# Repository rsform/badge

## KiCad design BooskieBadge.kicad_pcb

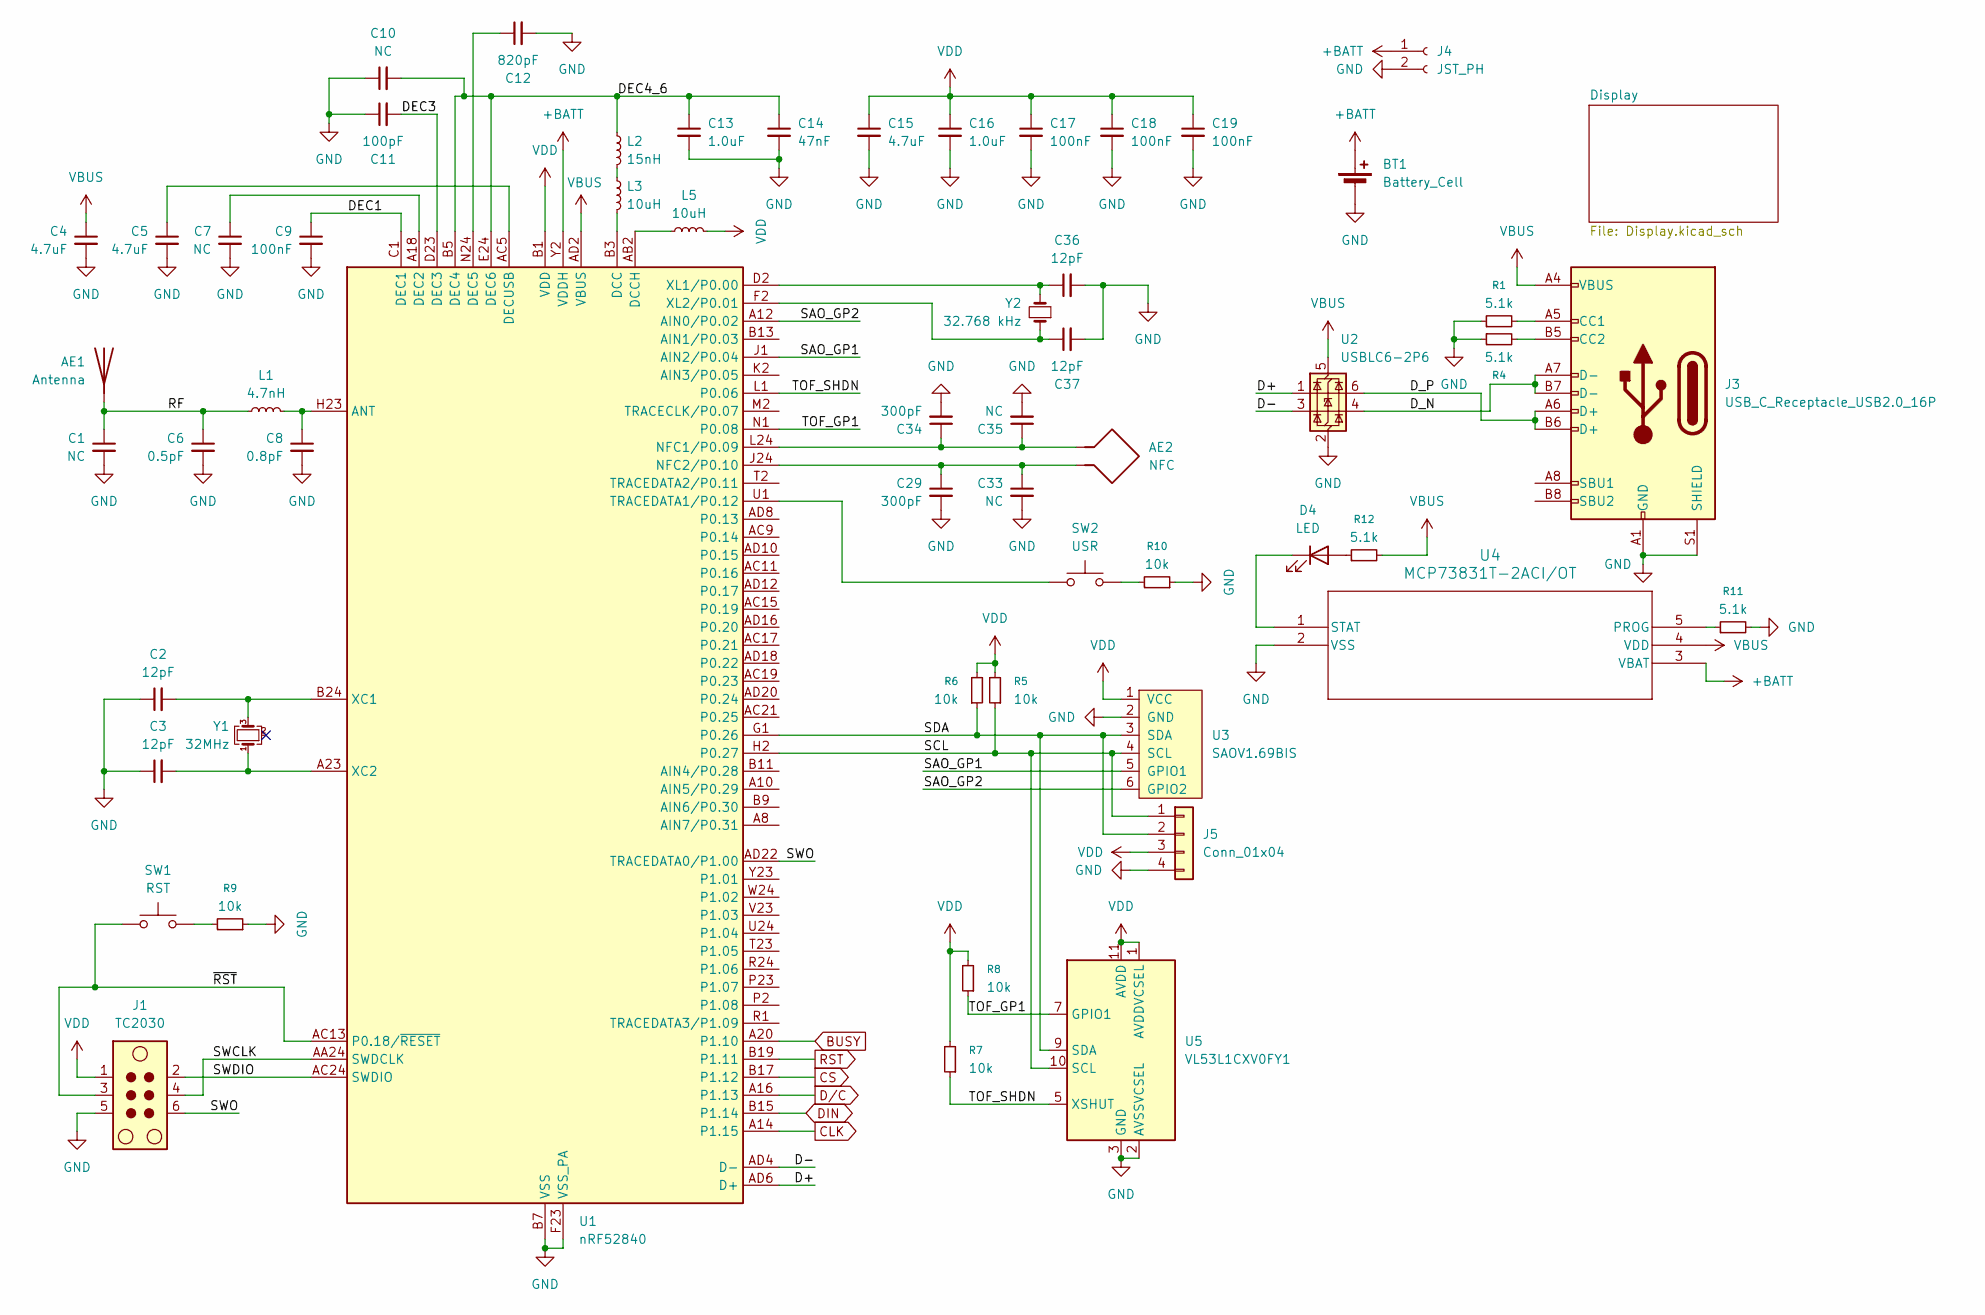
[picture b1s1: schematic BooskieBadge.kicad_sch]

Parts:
AE1: Antenna; 2.4GHz-meander-antenna-v2
AE2: NFC; NFC_ANTENNA
BT1: Battery_Cell; BAT_HOLDER_2032SMD
C1, C7, C10, C33, C35: NC; C_0402_1005Metric
C2, C3, C36, C37: 12pF; C_0402_1005Metric
C4, C5, C15: 4.7uF; C_0603_1608Metric
C6: 0.5pF; C_0402_1005Metric
C8: 0.8pF; C_0402_1005Metric
C9, C17, C18, C19: 100nF; C_0402_1005Metric
C11: 100pF; C_0402_1005Metric
C12: 820pF; C_0402_1005Metric
C13, C16: 1.0uF; C_0603_1608Metric
C14: 47nF; C_0402_1005Metric
C29, C34: 300pF; C_0402_1005Metric
D4: LED; LED_LB Q39G-L2OO-35-1_OSR
J1: TC2030; Tag-Connect_TC2030-IDC-NL_2x03_P1.27mm_Vertical
J3: USB_C_Receptacle_USB2.0_16P; USB_C_Receptacle_JAE_DX07S016JA1R1500
J4: JST_PH; JST_PH_S2B-PH-K_1x02_P2.00mm_Horizontal
J5: Conn_01x04; JST_SH_SM04B-SRSS-TB_1x04-1MP_P1.00mm_Horizontal
L1: 4.7nH; L_0402_1005Metric
L2: 15nH; L_0402_1005Metric
L3, L5: 10uH; L_0603_1608Metric
R1, R4, R11, R12: 5.1k; R_0402_1005Metric
R5, R6, R7, R8, R9, R10: 10k; R_0402_1005Metric
SW1: RST; SW_Push_1P1T_NO_CK_KMR2
SW2: USR; SW_Push_1P1T_NO_CK_KMR2
U1: nRF52840; Nordic_AQFN-73-1EP_7x7mm_P0.5mm
U2: USBLC6-2P6; SOT-666
U3: SAOV1.69BIS; Simple_Addon_v2-BADGE-2x3
U4: MCP73831T-2ACI/OT; SOT-23-5_MC_MCH
U5: VL53L1CXV0FY1; ST_VL53L1x
Y1: 32MHz; Crystal_SMD_2016-4Pin_2.0x1.6mm
Y2: 32.768 kHz; Crystal_SMD_3215-2Pin_3.2x1.5mm

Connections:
+BATT: BT1.1 (+), J4.1, U1.Y2 (VDDH), U4.3 (VBAT)
/D+: U1.AD6 (D+), U2.1 (I/O1)
/D-: U1.AD4 (D-), U2.3 (I/O2)
/DEC1: C9.1, U1.C1 (DEC1)
/DEC3: C11.2, U1.D23 (DEC3)
/DEC4_6: C10.2, C13.1, C14.1, L2.1, U1.B5 (DEC4), U1.E24 (DEC6)
/D_N: J3.A7 (D-), J3.B7 (D-), U2.4 (I/O2)
/D_P: J3.A6 (D+), J3.B6 (D+), U2.6 (I/O1)
/RF: AE1.1 (A), C1.1, C6.1, L1.1
/SAO_GP1: U1.J1 (AIN2/P0.04), U3.5 (GPIO1)
/SAO_GP2: U1.A12 (AIN0/P0.02), U3.6 (GPIO2)
/SCL: J5.1, R5.1, U1.H2 (P0.27), U3.4 (SCL), U5.10 (SCL)
/SDA: J5.2, R6.1, U1.G1 (P0.26), U3.3 (SDA), U5.9 (SDA)
/SWCLK: J1.4, U1.AA24 (SWDCLK)
/SWDIO: J1.2, U1.AC24 (SWDIO)
/SWO: J1.6, U1.AD22 (TRACEDATA0/P1.00)
/TOF_GP1: R8.1, U1.N1 (P0.08), U5.7 (GPIO1)
/TOF_SHDN: R7.1, U1.L1 (P0.06), U5.5 (XSHUT)
/~RST: J1.3, SW1.1, U1.AC13 (P0.18/~RESET)
BUSY: U1.A20 (P1.10); also elsewhere on the board
CLK: U1.A14 (P1.15); also elsewhere on the board
CS: U1.B17 (P1.12); also elsewhere on the board
DIN: U1.B15 (P1.14); also elsewhere on the board
D/C: U1.A16 (P1.13); also elsewhere on the board
GND: BT1.2 (-), C1.2, C2.1, C3.1, C4.2, C5.2, C6.2, C7.2, C8.2, C9.2, C10.1, C11.1, C12.2, C13.2, C14.2, C15.2, C16.2, C17.2, C18.2, C19.2, C29.2, C33.2, C34.2, C35.2, C36.2, C37.2, J1.5, J3.A1 (GND), J3.A12 (GND), J3.B1 (GND), J3.B12 (GND), J3.S1 (SHIELD), J4.2, J5.4, R1.1, R4.1, R9.1, R10.1, R11.2, U1.B7 (VSS), U1.EP (VSS), U1.F23 (VSS_PA), U2.2 (GND), U3.2 (GND), U4.2 (VSS), U5.2 (AVSSVCSEL), U5.3 (GND), U5.4 (GND), U5.6 (GND), U5.12 (GND); also elsewhere on the board
unnamed: D4.2 (A), R12.1
unnamed: D4.1 (K), U4.1 (STAT)
unnamed: J3.A5 (CC1), R1.2
unnamed: J3.B5 (CC2), R4.2
unnamed: L2.2, L3.1
unnamed: R9.2, SW1.2
unnamed: R10.2, SW2.2
unnamed: C8.1, L1.2, U1.H23 (ANT)
unnamed: L3.2, U1.B3 (DCC)
unnamed: L5.2, U1.AB2 (DCCH)
unnamed: C7.1, U1.A18 (DEC2)
unnamed: C12.1, U1.N24 (DEC5)
unnamed: C5.1, U1.AC5 (DECUSB)
unnamed: AE2.1, C34.1, C35.1, U1.L24 (NFC1/P0.09)
unnamed: AE2.2, C29.1, C33.1, U1.J24 (NFC2/P0.10)
unnamed: SW2.1, U1.U1 (TRACEDATA1/P0.12)
unnamed: C2.2, U1.B24 (XC1), Y1.3
unnamed: C3.2, U1.A23 (XC2), Y1.1
unnamed: C36.1, U1.D2 (XL1/P0.00), Y2.2
unnamed: C37.1, U1.F2 (XL2/P0.01), Y2.1
unnamed: R11.1, U4.5 (PROG)
RST: U1.B19 (P1.11); also elsewhere on the board
VBUS: C4.1, J3.A4 (VBUS), J3.A9 (VBUS), J3.B4 (VBUS), J3.B9 (VBUS), R12.2, U1.AD2 (VBUS), U2.5 (VBUS), U4.4 (VDD)
VDD: C15.1, C16.1, C17.1, C18.1, C19.1, J1.1, J5.3, L5.1, R5.2, R6.2, R7.2, R8.2, U1.A22 (VDD), U1.AD14 (VDD), U1.AD23 (VDD), U1.B1 (VDD), U1.W1 (VDD), U3.1 (VCC), U5.1 (AVDDVCSEL), U5.11 (AVDD); also elsewhere on the board

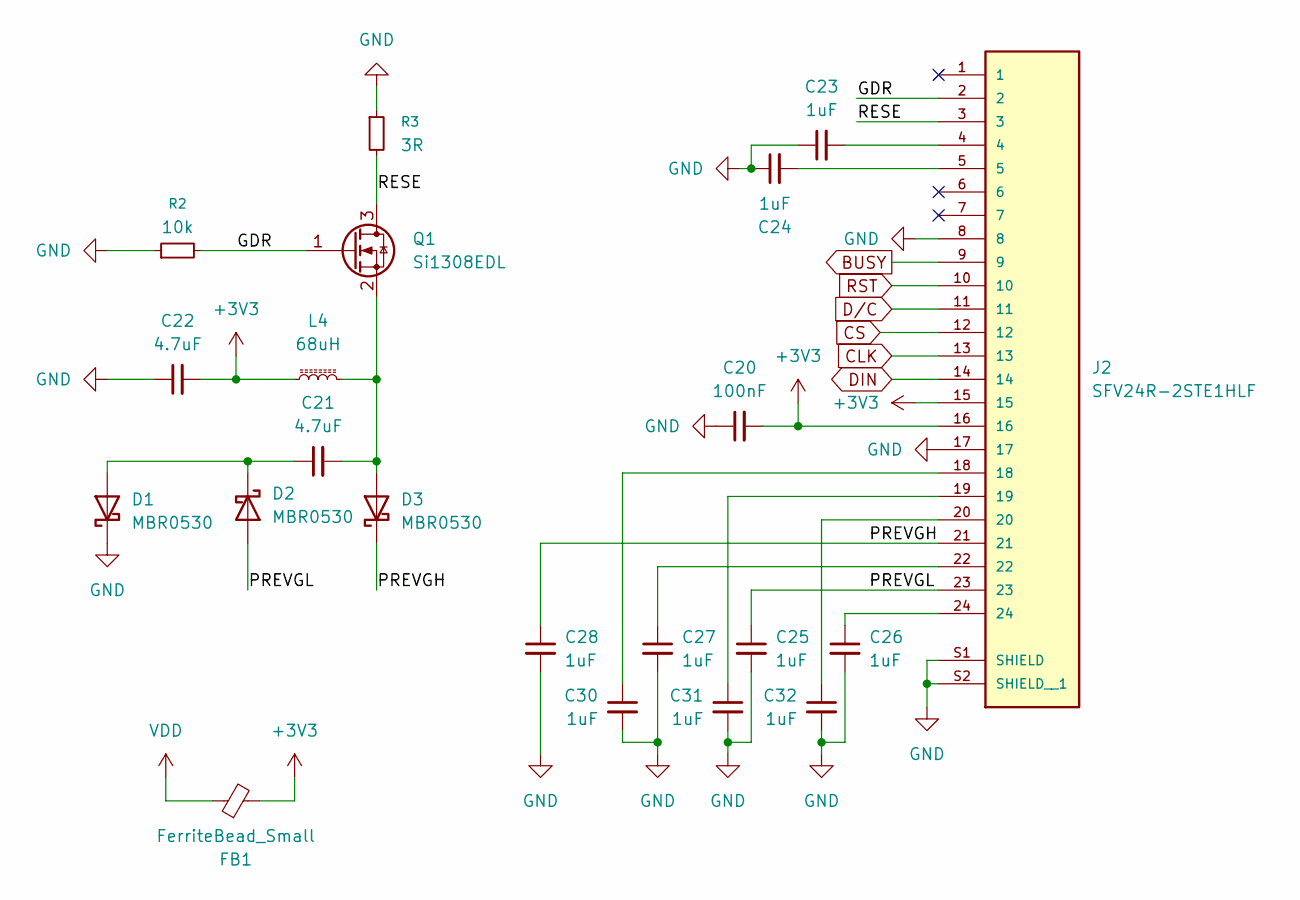
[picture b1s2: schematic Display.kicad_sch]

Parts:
C20: 100nF; C_0402_1005Metric
C21, C22: 4.7uF; C_0603_1608Metric
C23, C24, C25, C26, C27, C28, C30, C31, C32: 1uF; C_0603_1608Metric
D1, D2, D3: MBR0530; D_SOD-123
FB1: FerriteBead_Small; L_0603_1608Metric
J2: SFV24R-2STE1HLF; AMPHENOL_SFV24R-2STE1HLF; PARTREV C
L4: 68uH; L_0603_1608Metric
Q1: Si1308EDL; SOT-323_SC-70
R2: 10k; R_0402_1005Metric
R3: 3R; R_0402_1005Metric

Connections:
+3V3: C20.2, C22.2, FB1.2, J2.15, J2.16, L4.1
/Display/GDR: J2.2, Q1.1 (G), R2.2
/Display/PREVGH: C28.1, D3.1 (K), J2.21
/Display/PREVGL: C25.1, D2.2 (A), J2.23
/Display/RESE: J2.3, Q1.3 (D), R3.2
BUSY: J2.9; also elsewhere on the board
CLK: J2.13; also elsewhere on the board
CS: J2.12; also elsewhere on the board
DIN: J2.14; also elsewhere on the board
D/C: J2.11; also elsewhere on the board
GND: C20.1, C22.1, C23.1, C24.1, C25.2, C26.2, C27.2, C28.2, C30.2, C31.2, C32.2, D1.1 (K), J2.8, J2.17, J2.S1 (SHIELD), J2.S2 (SHIELD__1), R2.1, R3.1; also elsewhere on the board
unnamed: C23.2, J2.4
unnamed: C24.2, J2.5
unnamed: C26.1, J2.24
unnamed: C27.1, J2.22
unnamed: C30.1, J2.18
unnamed: C31.1, J2.19
unnamed: C32.1, J2.20
unnamed: C21.1, D1.2 (A), D2.1 (K)
unnamed: C21.2, D3.2 (A), L4.2, Q1.2 (S)
RST: J2.10; also elsewhere on the board
VDD: FB1.1; also elsewhere on the board

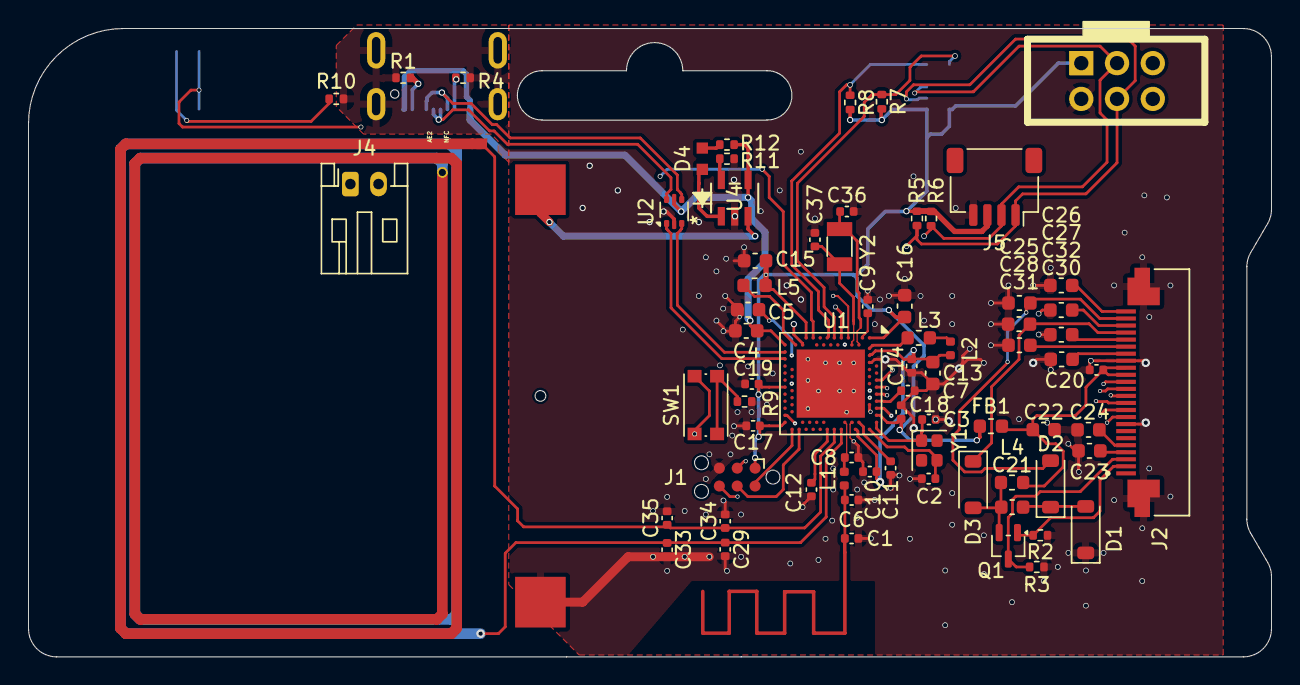
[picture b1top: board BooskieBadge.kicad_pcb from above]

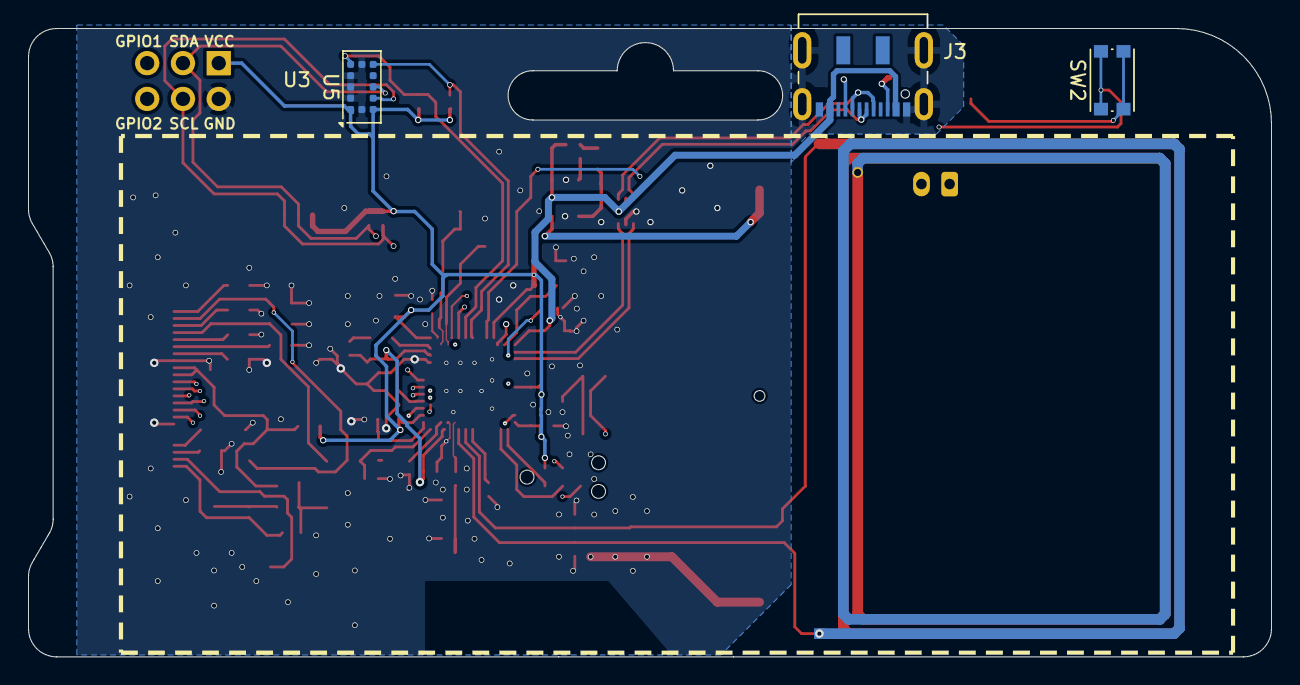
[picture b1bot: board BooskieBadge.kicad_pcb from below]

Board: 4 copper layers, 88.3 x 44.6 mm, 77 parts (3 on the bottom side), 63 nets.

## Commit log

2026-01-30 initial design
2026-01-30 pcb first pass
2026-01-30 cleaned up some grounds
2026-01-31 screwing around with ports and stuff
2026-01-31 rtc crystal
2026-01-31 time-of-flight, plus usb, plus li-ion option
2026-01-31 bit of clean-up
2026-02-01 board edges
2026-02-17 feat: add hw-preview GitHub Actions workflow
